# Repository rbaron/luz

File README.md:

# luz
An experiment in USB-C power delivery.

This repo contains printed circuit board fabrication files and firmware sample for a basic USB-C power delivery "trigger board" with an accompanying ESP32.

## Hardware
The CYPD3177 IC is used to negotiate power contracts with USB-C power supplies, and communicates with the onboard ESP32 via I2C for control and monitoring.

Once the required power delivery contract is successfully negotiated, the ESP32 may control two MOSFET channels to switch power to two different loads. The original use case is to deliver 12 V @ 3 A to LED strips, but any load up to 3A and 20V may be used in principle.

### Main Components
- [CYPD3177](https://www.infineon.com/cms/en/product/universal-serial-bus/usb-c-charging-port-controllers/ez-pd-barrel-connector-replacement-bcr/cypd3177-24lqxq/) USB-C PD controller
- ESP32-WROOM-32
  - For this prototype I used this older module since I still have a bunch of them around.

## Software
The CYPD3177 is configured during runtime via I2C. I implemented the `cypd3177` component in an [ESPHome](https://esphome.io/) fork (at [rbaron/esphome/cypd3177](https://github.com/rbaron/esphome/tree/cypd3177)).

In this repo there are sample `yaml` files under [./code/esphome](./code/esphome) that uses the `cypd3177` as an external component.

To configure a power delivery contract, set up the `cypd3177` component in ESPHome as for example:
```yaml
cypd3177:
  interrupt_pin: GPIO23
  voltage: 9000 mV
  current: 1000 mA
```

## USB-C Power Delivery Support & Maximum Power
The CYPD3177 supports USB-C PD 3.0, but unfortunately does not support Programmable Power Supply (PPS) contracts. The board is a prototype, mostly for learning, designed to handle a maximum of only 3 A.

USB-C PD 3.0 mandates support for a few standard fixed power profiles, namely providing 5 V, 9 V, 15 V and 20 V. Some USB-C PD sources may also support 12 V. Enabling logging for the `cypd3177` component in ESPHome will show the power profiles supported by the source. For example:

```
16:08:41.416 -> [I][cypd3177.pdo:059]: Fixed PDO: 5000 mV, 3000 mA
16:08:41.416 -> [I][cypd3177.pdo:059]: Fixed PDO: 9000 mV, 3000 mA
16:08:41.416 -> [I][cypd3177.pdo:059]: Fixed PDO: 12000 mV, 2000 mA
16:08:41.416 -> [I][cypd3177.pdo:059]: Fixed PDO: 15000 mV, 2000 mA
16:08:41.416 -> [I][cypd3177.pdo:059]: Fixed PDO: 20000 mV, 1500 mA
16:08:41.416 -> [I][cypd3177.pdo:066]: Augmented SPR_PPS PDO: 3300 - 11000 mV, 3000 mA
```

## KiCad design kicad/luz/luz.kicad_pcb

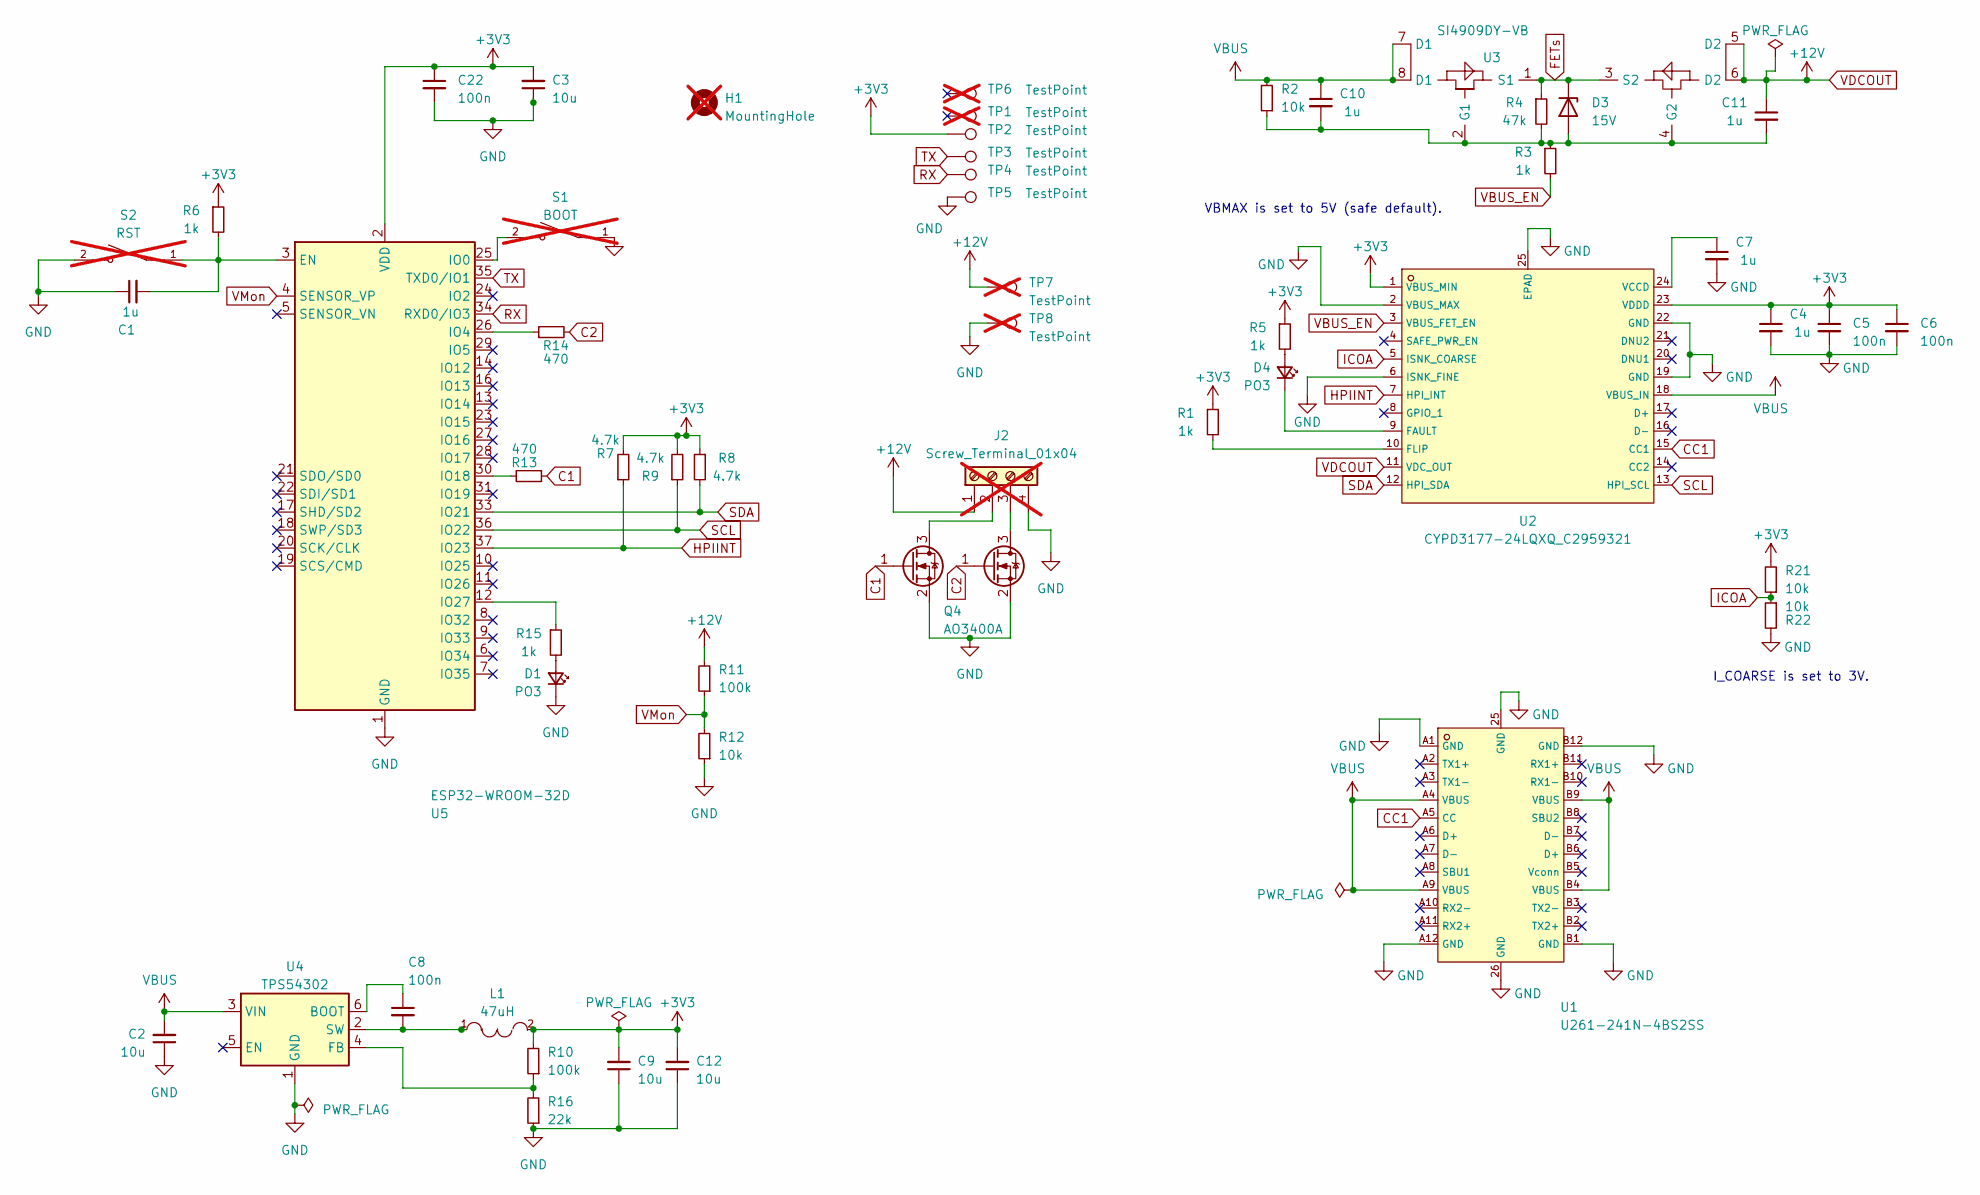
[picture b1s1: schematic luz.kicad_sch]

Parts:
C1, C4, C7, C10, C11: 1u; C_0402_1005Metric; LCSC C52923
C2, C3, C9, C12: 10u; C_0603_1608Metric; LCSC C194427
C5, C6, C8, C22: 100n; C_0402_1005Metric; LCSC C77020
D1, D4: PO3; LED_0603_1608Metric; LCSC C2286
D3: 15V; D_SOD-323; LCSC C131825
H1: MountingHole; MountingHole_2.2mm_M2_Pad_Via; not fitted
J2: Screw_Terminal_01x04; TerminalBlock_Phoenix_MKDS-1,5-4_1x04_P5.00mm_Horizontal; not fitted
L1: 47uH; IND-SMD_L4.0-W4.0_SLS3DXX; LCSC C54731
Q1, Q4: AO3400A; SOT-23; LCSC C20917
R1, R3, R5, R6, R15: 1k; R_0402_1005Metric; LCSC C11702
R2, R12, R21, R22: 10k; R_0402_1005Metric; LCSC C25744
R4: 47k; R_0402_1005Metric; LCSC C25792
R7, R8, R9: 4.7k; R_0402_1005Metric; LCSC C25900
R10, R11: 100k; R_0402_1005Metric; LCSC C25741
R13, R14: 470; R_0402_1005Metric; LCSC C25117
R16: 22k; R_0402_1005Metric; LCSC C25768
S1: BOOT; SW_B3U-1000P; LCSC C231329; not fitted
S2: RST; SW_B3U-1000P; LCSC C231329; not fitted
TP1, TP6: TestPoint; TestPoint_Pad_D1.5mm; not fitted
TP2, TP3, TP4, TP5: TestPoint; TestPoint_Pad_D1.5mm
TP7, TP8: TestPoint; TestPoint_Pad_4.0x4.0mm; not fitted
U1: U261-241N-4BS2SS; USB-C-SMD_U261-241N-4BS2SS; LCSC C2938596
U2: CYPD3177-24LQXQ_C2959321; TQFN-24_L4.0-W4.0-P0.50-TL-EP2.8; LCSC C2959321
U3: SI4909DY-VB; SO-8_L4.9-W3.9-P1.27-LS5.9-BL; LCSC C710072
U4: TPS54302; SOT-23-6; LCSC C311983
U5: ESP32-WROOM-32D

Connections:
+3V3: C3.2, C4.1, C5.1, C6.1, C9.2, C12.2, C22.1, L1.2, R1.1, R5.1, R6.1, R7.2, R8.1, R9.2, R10.2, R21.2, TP2.1, U2.1 (VBUS_MIN), U2.23 (VDDD), U5.2 (VDD)
C1: Q4.1 (G), R13.1
C2: Q1.1 (G), R14.2
CC1: U1.A5 (CC), U2.15 (CC1)
FETs: D3.1 (K), R4.1, U3.1 (S1), U3.3 (S2)
GND: C1.1, C2.1, C3.1, C4.2, C5.2, C6.2, C7.2, C9.1, C12.1, C22.2, D1.1 (K), J2.4, Q1.2 (S), Q4.2 (S), R12.1, R16.1, R22.2, S1.1, S2.2, TP5.1, TP8.1, U1.25 (GND), U1.26 (GND), U1.A1 (GND), U1.A12 (GND), U1.B1 (GND), U1.B12 (GND), U2.2 (VBUS_MAX), U2.6 (ISNK_FINE), U2.19 (GND), U2.22 (GND), U2.25 (EPAD), U4.1 (GND), U5.1 (GND), U5.15 (GND), U5.38 (GND), U5.39 (GND)
HPIINT: R7.1, U2.7 (HPI_INT), U5.37 (IO23)
ICOA: R21.1, R22.1, U2.5 (ISNK_COARSE)
unnamed: D1.2 (A), R15.2
unnamed: C10.2, C11.2, D3.2 (A), R2.1, R3.1, R4.2, U3.2 (G1), U3.4 (G2)
unnamed: D4.2 (A), R5.2
unnamed: D4.1 (K), U2.9 (FAULT)
unnamed: J2.2, Q4.3 (D)
unnamed: J2.3, Q1.3 (D)
unnamed: R1.2, U2.10 (FLIP)
unnamed: C7.1, U2.24 (VCCD)
unnamed: C8.1, U4.6 (BOOT)
unnamed: R10.1, R16.2, U4.4 (FB)
unnamed: C8.2, L1.1, U4.2 (SW)
unnamed: C1.2, R6.2, S2.1, U5.3 (EN)
unnamed: S1.2, U5.25 (IO0)
unnamed: R14.1, U5.26 (IO4)
unnamed: R13.2, U5.30 (IO18)
unnamed: R15.1, U5.12 (IO27)
RX: TP4.1, U5.34 (RXD0/IO3)
SCL: R9.1, U2.13 (HPI_SCL), U5.36 (IO22)
SDA: R8.2, U2.12 (HPI_SDA), U5.33 (IO21)
TX: TP3.1, U5.35 (TXD0/IO1)
VBUS: C2.2, C10.1, R2.2, U1.A4 (VBUS), U1.A9 (VBUS), U1.B4 (VBUS), U1.B9 (VBUS), U2.18 (VBUS_IN), U3.7 (D1), U3.8 (D1), U4.3 (VIN)
VBUS_EN: R3.2, U2.3 (VBUS_FET_EN)
VDCOUT: C11.1, J2.1, R11.2, TP7.1, U2.11 (VDC_OUT), U3.5 (D2), U3.6 (D2)
VMon: R11.1, R12.2, U5.4 (SENSOR_VP)

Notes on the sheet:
VBMAX is set to 5V (safe default).
I_COARSE is set to 3V.

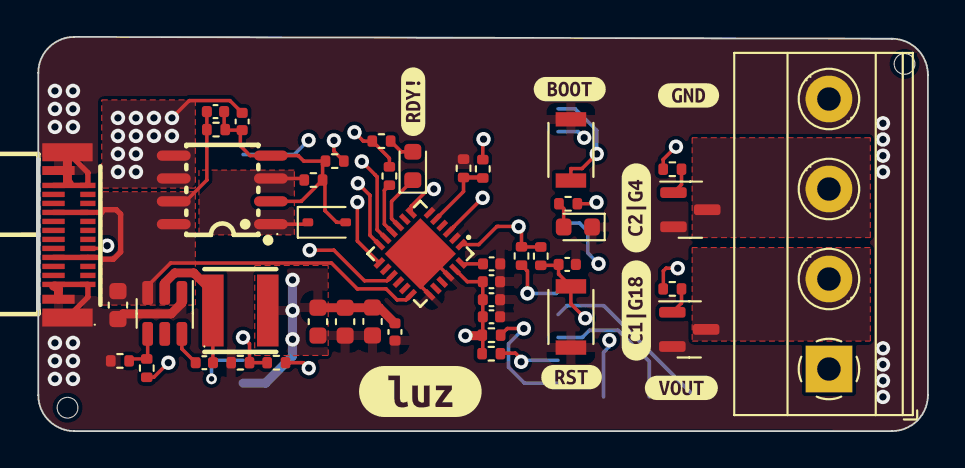
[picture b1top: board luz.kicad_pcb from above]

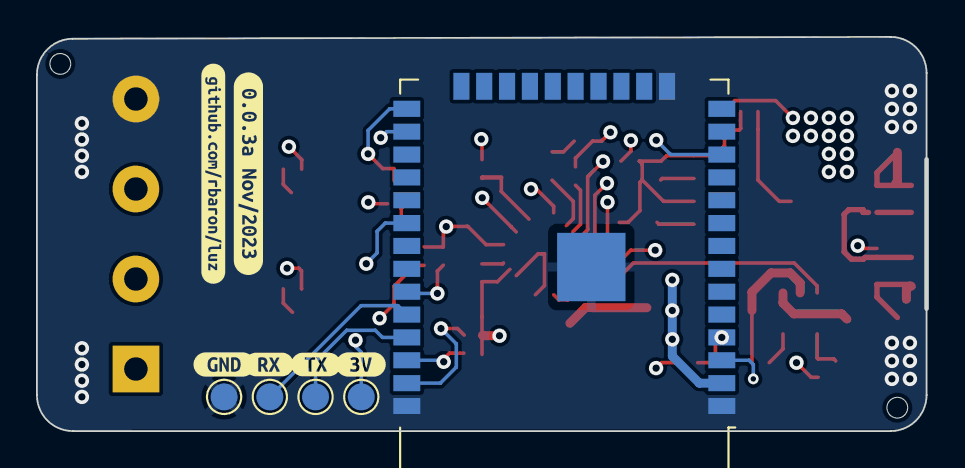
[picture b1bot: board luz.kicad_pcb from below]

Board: 4 copper layers, 49.3 x 21.7 mm, 63 parts (11 on the bottom side), 32 nets.

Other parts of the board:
kibuzzard-655BB0B1: G***; kibuzzard-655BB0B1
kibuzzard-655BB0BF: G***; kibuzzard-655BB0BF
kibuzzard-655BB09E: G***; kibuzzard-655BB09E
kibuzzard-655BB076: G***; kibuzzard-655BB076
kibuzzard-655BB97E: G***; kibuzzard-655BB97E
kibuzzard-655BB98B: G***; kibuzzard-655BB98B
kibuzzard-655BB458: G***; kibuzzard-655BB458
kibuzzard-655BB485: G***; kibuzzard-655BB485
kibuzzard-655BBA1E: G***; kibuzzard-655BBA1E
kibuzzard-655BBA6D: G***; kibuzzard-655BBA6D
kibuzzard-655BBA49: G***; kibuzzard-655BBA49
kibuzzard-658ADB24: G***; kibuzzard-658ADB24
kibuzzard-658AE3F9: G***; kibuzzard-658AE3F9
kibuzzard-658AE32D: G***; kibuzzard-658AE32D

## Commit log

2023-11-13 Initial routing
2023-11-13 Route DISCH pin through 1k resistor
2023-11-13 Pull down RST from STUSB45, as suggested by datasheet
2023-11-13 Connect shield
2023-11-13 Added missing LCSC numbers
2023-11-14 Plotted files for production
2023-11-14 Move notes.md to this repo
2023-11-20 Routed new version with ESP32-WROOM
2023-11-20 Better ground plane
2023-11-20 Fix schematic DRC
2023-11-20 Naming schematic values
2023-11-20 Sent 0.0.2a for production
2023-11-22 Moar notes
2023-12-02 Some notes on devcontainers
2023-12-18 Some notes
2023-12-26 ez_pd => cypd3177
2023-12-26 Adds 470 resistors to N FET channel drivers' gates & fix VBUSMAX
2023-12-26 Plotted fab outputs for 0.0.3a
2023-12-26 README
2023-12-26 Cleanup
2023-12-26 Re-plotted fab files after making resistor designators invisible
2023-12-26 Typos
